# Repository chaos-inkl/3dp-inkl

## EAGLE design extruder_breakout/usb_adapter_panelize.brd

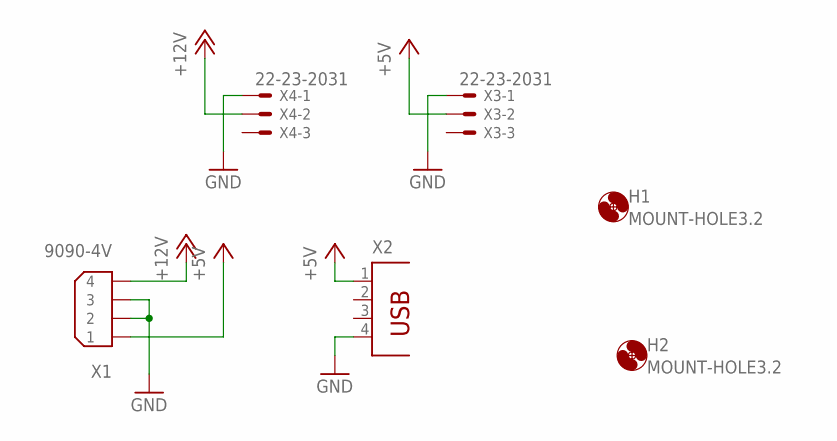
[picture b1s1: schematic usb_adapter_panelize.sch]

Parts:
H1, H2: MOUNT-HOLE3.2; 3,2
X1: 9090-4V
X2: PN87520
X3, X4: 22-23-2031

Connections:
+5V: X1.1, X2.1, X3.2
+12V: X1.4, X4.2
GND: X1.2, X1.3, X2.4, X3.1, X4.1

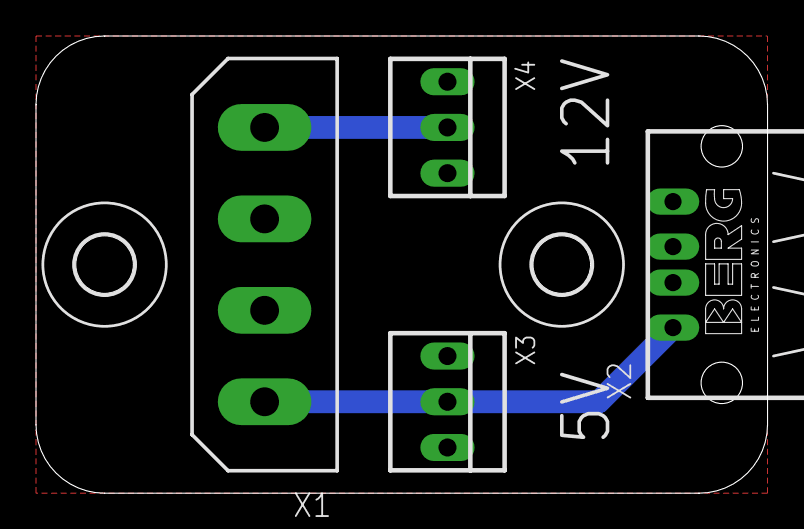
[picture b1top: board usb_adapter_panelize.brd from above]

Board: 2 copper layers, 40.6 x 25.4 mm, 6 parts (0 on the bottom side), 3 nets.

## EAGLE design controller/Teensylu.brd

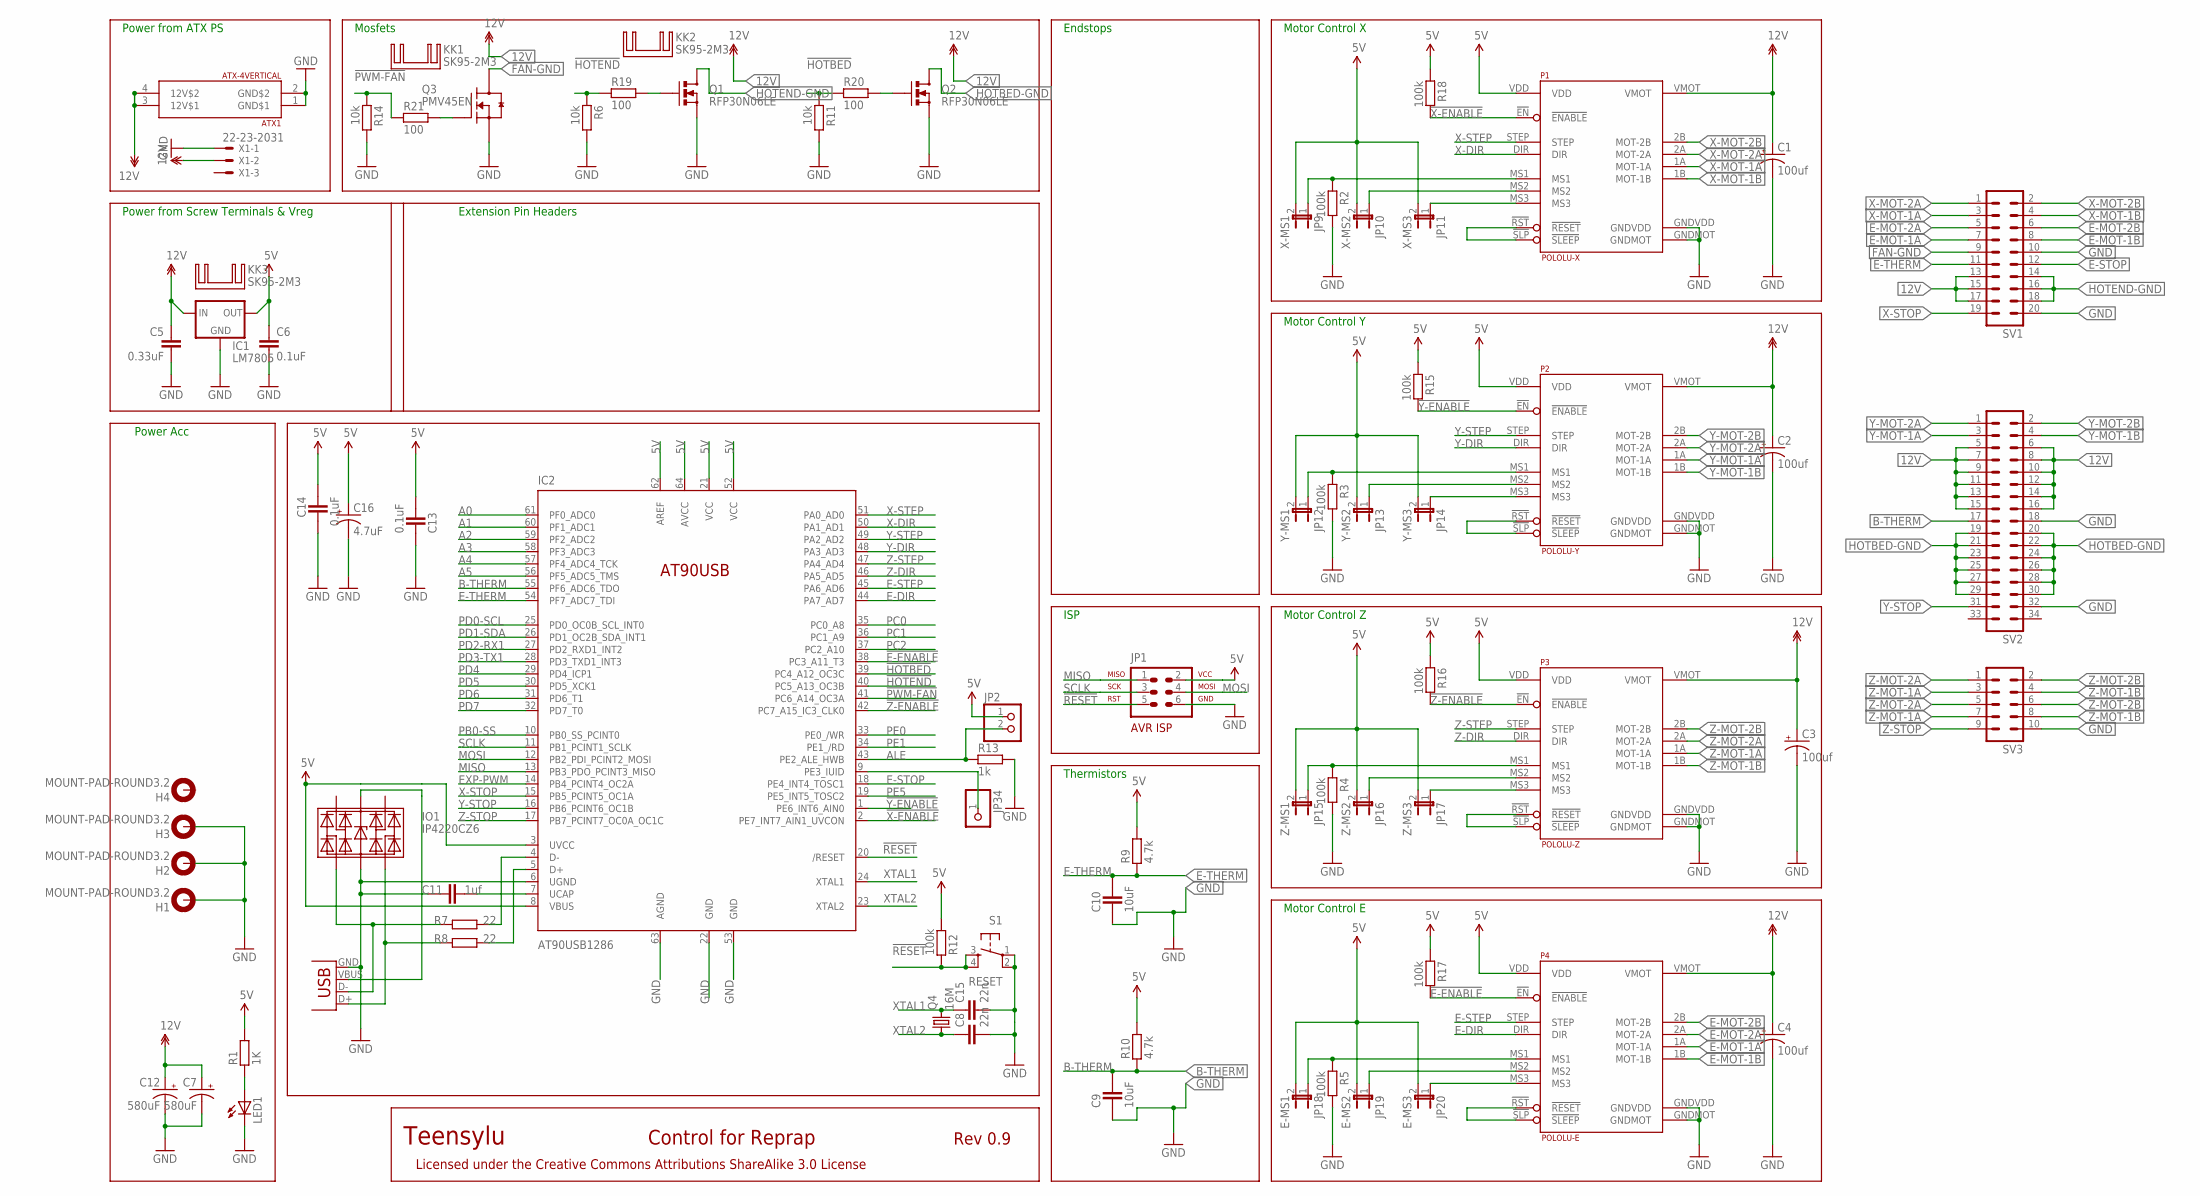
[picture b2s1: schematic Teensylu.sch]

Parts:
ATX1: ATX-4VERTICAL; MINIFITJR-4-VERTICAL
C1, C2, C3, C4: 100uf; CPOL-RADIAL-100UF-25V
C5: 0.33uF; CAP-PTH-SMALL2
C6: 0.1uF; CAP-PTH-SMALL2
C7, C12: 580uF; CPOL-RADIAL-1000UF-25V
C8, C15: 22n; C0603
C9, C10: 10uF; CAPC1608X92N
C11: 1uf; CAPC1608X92N
C13, C14: 0.1uF; CAPC1608X92N
C16: 4.7uF; CPOL-RADIAL-10UF-25V
H1, H2, H3, H4: MOUNT-PAD-ROUND3.2; 3,2-PAD
IC1: LM7805; 78XXL-CUSTOM
IC2: AT90USB1286; TQFP64-2
IO1: IP4220CZ6; SOT23-6
J1: USB; USB-B-PTH
JP1: AVR-ISP-6VERT; AVR-ISP-6
JP2: PINHD-1X2; 1X02
JP9: X-MS1; 1X02
JP10: X-MS2; 1X02
JP11: X-MS3; 1X02
JP12: Y-MS1; 1X02
JP13: Y-MS2; 1X02
JP14: Y-MS3; 1X02
JP15: Z-MS1; 1X02
JP16: Z-MS2; 1X02
JP17: Z-MS3; 1X02
JP18: E-MS1; 1X02
JP19: E-MS2; 1X02
JP20: E-MS3; 1X02
JP34: PINHD-1X1; 1X01
KK1, KK2, KK3: SK95-2M3
LED1: LED5MM
P1: POLOLU-X; POLOLU-ALLEGRO-PTH
P2: POLOLU-Y; POLOLU-ALLEGRO-PTH
P3: POLOLU-Z; POLOLU-ALLEGRO-PTH
P4: POLOLU-E; POLOLU-ALLEGRO-PTH
Q1, Q2: RFP30N06LE; TO220V
Q3: PMV45EN; SOT95P280X135-3N
Q4: 16M; HC49U-V
R1: 1K; RESC1608X55N
R2, R3, R4, R5, R12, R15, R16, R17, R18: 100k; RESC1608X55N
R6, R11, R14: 10k; RESC1608X55N
R7, R8: 22; RESC1608X55N
R9, R10: 4.7k; RESC1608X55N
R13: 1k; RESC1608X55N
R19, R20, R21: 100; RESC1608X55N
S1: RESET; TACTILE-PTH
SV1: ML20L
SV2: ML34L
SV3: ML10L
X1: 22-23-2031

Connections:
5V: C6.1, C13.2, C14.1, C16.1 (+), IC1.OUT, IC2.3 (UVCC), IC2.8 (VBUS), IC2.21 (VCC), IC2.52 (VCC), IC2.62 (AREF), IC2.64 (AVCC), JP1.2, JP2.1, JP9.2, JP10.2, JP11.2, JP12.2, JP13.2, JP14.2, JP15.2, JP16.2, JP17.2, JP18.2, JP19.2, JP20.2, P1.VDD, P2.VDD, P3.VDD, P4.VDD, R1.2, R9.2, R10.2, R12.2, R15.1, R16.1, R17.1, R18.1
12V: ATX1.3 (12V$1), ATX1.4 (12V$2), C1.1 (+), C2.1 (+), C3.1 (+), C4.1 (+), C5.1, C7.1 (+), C12.1 (+), IC1.IN, P1.VMOT, P2.VMOT, P3.VMOT, P4.VMOT, SV1.13, SV1.15, SV1.17, SV2.5, SV2.6, SV2.7, SV2.8, SV2.9, SV2.10, SV2.11, SV2.12, SV2.13, SV2.14, SV2.15, SV2.16, X1.2
!E-ENABLE: IC2.38 (PC3_A11_T3), P4.!EN (!ENABLE), R17.2
!HOTBED: IC2.39 (PC4_A12_OC3C), R11.1, R20.1
!HOTEND: IC2.40 (PC5_A13_OC3B), R6.1, R19.1
!PWM-FAN: IC2.41 (PC6_A14_OC3A), R14.1, R21.1
!RESET: IC2.20 (/RESET), JP1.5, R12.1, S1.3, S1.4
!X-ENABLE: IC2.2 (PE7_INT7_AIN1_UVCON), P1.!EN (!ENABLE), R18.2
!Y-ENABLE: IC2.1 (PE6_INT6_AIN0), P2.!EN (!ENABLE), R15.2
!Z-ENABLE: IC2.42 (PC7_A15_IC3_CLK0), P3.!EN (!ENABLE), R16.2
A0: IC2.61 (PF0_ADC0)
A1: IC2.60 (PF1_ADC1)
A2: IC2.59 (PF2_ADC2)
A3: IC2.58 (PF3_ADC3)
A4: IC2.57 (PF4_ADC4_TCK)
A5: IC2.56 (PF5_ADC5_TMS)
ALE: IC2.43 (PE2_ALE_HWB), JP2.2, R13.1
B-THERM: C9.2, IC2.55 (PF6_ADC6_TDO), R10.1, SV2.17
E-DIR: IC2.44 (PA7_AD7), P4.DIR
E-MOT-1A: P4.1A (MOT-1A), SV1.7
E-MOT-1B: P4.1B (MOT-1B), SV1.8
E-MOT-2A: P4.2A (MOT-2A), SV1.5
E-MOT-2B: P4.2B (MOT-2B), SV1.6
E-MS1: JP18.1, P4.MS1, R5.1
E-MS2: JP19.1, P4.MS2
E-MS3: JP20.1, P4.MS3
E-RESETSLEEP: P4.!RST (!RESET), P4.!SLP (!SLEEP)
E-STEP: IC2.45 (PA6_AD6), P4.STEP
E-STOP: IC2.18 (PE4_INT4_TOSC1), SV1.12
E-THERM: C10.2, IC2.54 (PF7_ADC7_TDI), R9.1, SV1.11
EXP-PWM: IC2.14 (PB4_PCINT4_OC2A)
FAN-GND: Q3.3 (D), SV1.9
GND: ATX1.1 (GND$1), ATX1.2 (GND$2), C1.2 (-), C2.2 (-), C3.2 (-), C4.2 (-), C5.2, C6.2, C7.2 (-), C8.2, C9.1, C10.1, C11.1, C12.2 (-), C13.1, C14.2, C15.2, C16.2 (-), H1.B3,2, H2.B3,2, H3.B3,2, IC1.GND, IC2.6 (UGND), IC2.22 (GND), IC2.53 (GND), IC2.63 (AGND), IO1.2 (GND), J1.GND, JP1.6, LED1.K (C), P1.GNDMOT, P1.GNDVDD, P2.GNDMOT, P2.GNDVDD, P3.GNDMOT, P3.GNDVDD, P4.GNDMOT, P4.GNDVDD, Q1.3 (S), Q2.3 (S), Q3.2 (S), R2.2, R3.2, R4.2, R5.2, R6.2, R11.2, R13.2, R14.2, S1.1, S1.2, SV1.10, SV1.20, SV2.18, SV2.32, SV3.10, X1.1
HOTBED-GND: Q2.2 (D), SV2.19, SV2.20, SV2.21, SV2.22, SV2.23, SV2.24, SV2.25, SV2.26, SV2.27, SV2.28, SV2.29, SV2.30
HOTEND-GND: Q1.2 (D), SV1.14, SV1.16, SV1.18
MISO: IC2.13 (PB3_PDO_PCINT3_MISO), JP1.1
MOSI: IC2.12 (PB2_PDI_PCINT2_MOSI), JP1.4
unnamed: LED1.A, R1.1
unnamed: IO1.4 (C), J1.D-, R7.1
unnamed: IC2.4 (D-), R7.2
unnamed: IC2.5 (D+), R8.2
unnamed: IO1.6 (D), J1.D+, R8.1
unnamed: IO1.5 (UCC), J1.VBUS
unnamed: IC2.9 (PE3_IUID), JP34.1
unnamed: C11.2, IC2.7 (UCAP)
unnamed: Q3.1 (G), R21.2
unnamed: Q1.1 (G), R19.2
unnamed: Q2.1 (G), R20.2
PB0-SS: IC2.10 (PB0_SS_PCINT0)
PC0: IC2.35 (PC0_A8)
PC1: IC2.36 (PC1_A9)
PC2: IC2.37 (PC2_A10)
PD0-SCL: IC2.25 (PD0_OC0B_SCL_INT0)
PD1-SDA: IC2.26 (PD1_OC2B_SDA_INT1)
PD2-RX1: IC2.27 (PD2_RXD1_INT2)
PD3-TX1: IC2.28 (PD3_TXD1_INT3)
PD4: IC2.29 (PD4_ICP1)
PD5: IC2.30 (PD5_XCK1)
PD6: IC2.31 (PD6_T1)
PD7: IC2.32 (PD7_T0)
PE0: IC2.33 (PE0_/WR)
PE1: IC2.34 (PE1_/RD)
PE5: IC2.19 (PE5_INT5_TOSC2)
SCLK: IC2.11 (PB1_PCINT1_SCLK), JP1.3
X-DIR: IC2.50 (PA1_AD1), P1.DIR
X-MOT-1A: P1.1A (MOT-1A), SV1.3
X-MOT-1B: P1.1B (MOT-1B), SV1.4
X-MOT-2A: P1.2A (MOT-2A), SV1.1
X-MOT-2B: P1.2B (MOT-2B), SV1.2
X-MS1: JP9.1, P1.MS1, R2.1
X-MS2: JP10.1, P1.MS2
X-MS3: JP11.1, P1.MS3
X-RESETSLEEP: P1.!RST (!RESET), P1.!SLP (!SLEEP)
X-STEP: IC2.51 (PA0_AD0), P1.STEP
X-STOP: IC2.15 (PB5_PCINT5_OC1A), SV1.19
XTAL1: C15.1, IC2.24 (XTAL1), Q4.2
XTAL2: C8.1, IC2.23 (XTAL2), Q4.1
Y-DIR: IC2.48 (PA3_AD3), P2.DIR
Y-MOT-1A: P2.1A (MOT-1A), SV2.3
Y-MOT-1B: P2.1B (MOT-1B), SV2.4
Y-MOT-2A: P2.2A (MOT-2A), SV2.1
Y-MOT-2B: P2.2B (MOT-2B), SV2.2
Y-MS1: JP12.1, P2.MS1, R3.1
Y-MS2: JP13.1, P2.MS2
Y-MS3: JP14.1, P2.MS3
Y-RESETSLEEP: P2.!RST (!RESET), P2.!SLP (!SLEEP)
Y-STEP: IC2.49 (PA2_AD2), P2.STEP
Y-STOP: IC2.16 (PB6_PCINT6_OC1B), SV2.31
Z-DIR: IC2.46 (PA5_AD5), P3.DIR
Z-MOT-1A: P3.1A (MOT-1A), SV3.3, SV3.7
Z-MOT-1B: P3.1B (MOT-1B), SV3.4, SV3.8
Z-MOT-2A: P3.2A (MOT-2A), SV3.1, SV3.5
Z-MOT-2B: P3.2B (MOT-2B), SV3.2, SV3.6
Z-MS1: JP15.1, P3.MS1, R4.1
Z-MS2: JP16.1, P3.MS2
Z-MS3: JP17.1, P3.MS3
Z-RESETSLEEP: P3.!RST (!RESET), P3.!SLP (!SLEEP)
Z-STEP: IC2.47 (PA4_AD4), P3.STEP
Z-STOP: IC2.17 (PB7_PCINT7_OC0A_OC1C), SV3.9

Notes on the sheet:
Motor Control X
Motor Control Y
Motor Control Z
Motor Control E
ISP
Thermistors
Endstops
Mosfets
Power Acc
Teensylu
Rev 0.9
Control for Reprap
Licensed under the Creative Commons Attributions ShareAlike 3.0 License
Extension Pin Headers
Power from ATX PS
Power from Screw Terminals & Vreg

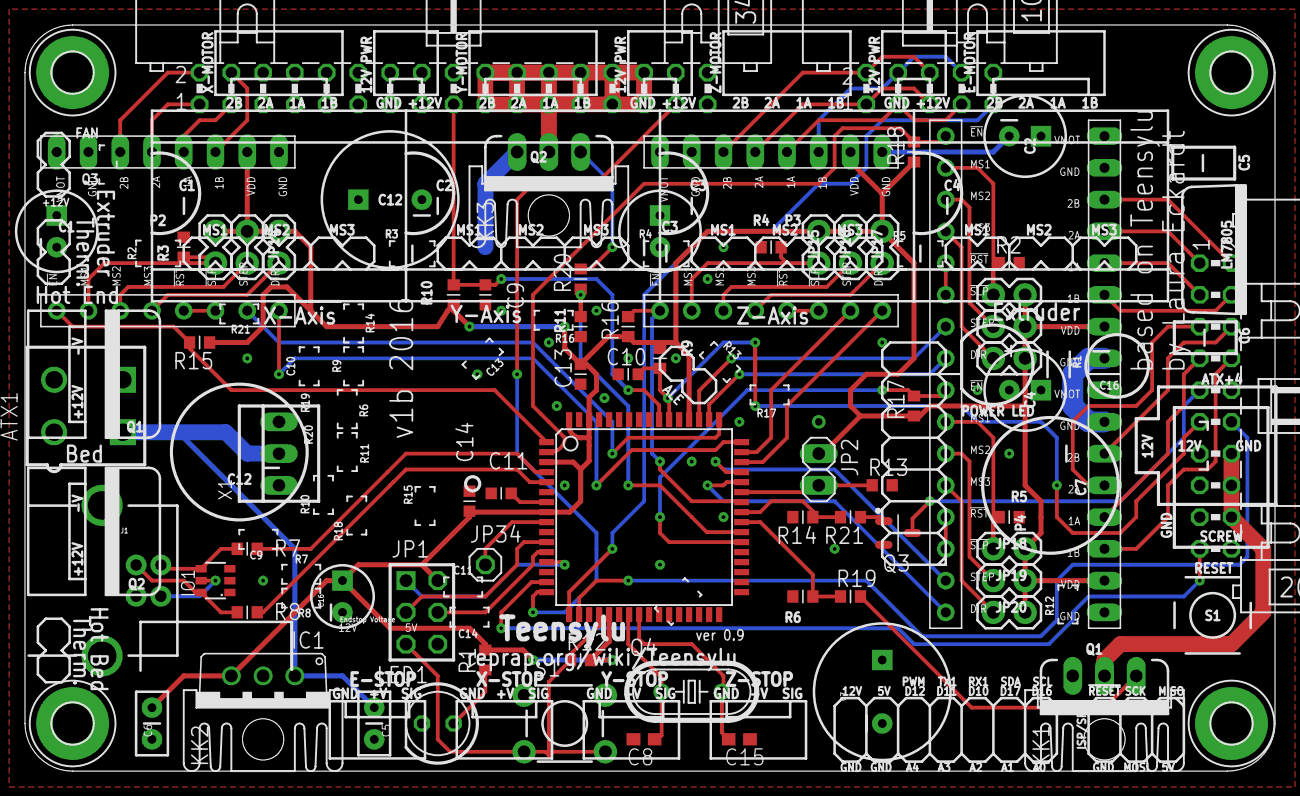
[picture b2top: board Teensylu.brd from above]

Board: 2 copper layers, 100.0 x 59.7 mm, 78 parts (0 on the bottom side), 77 nets.

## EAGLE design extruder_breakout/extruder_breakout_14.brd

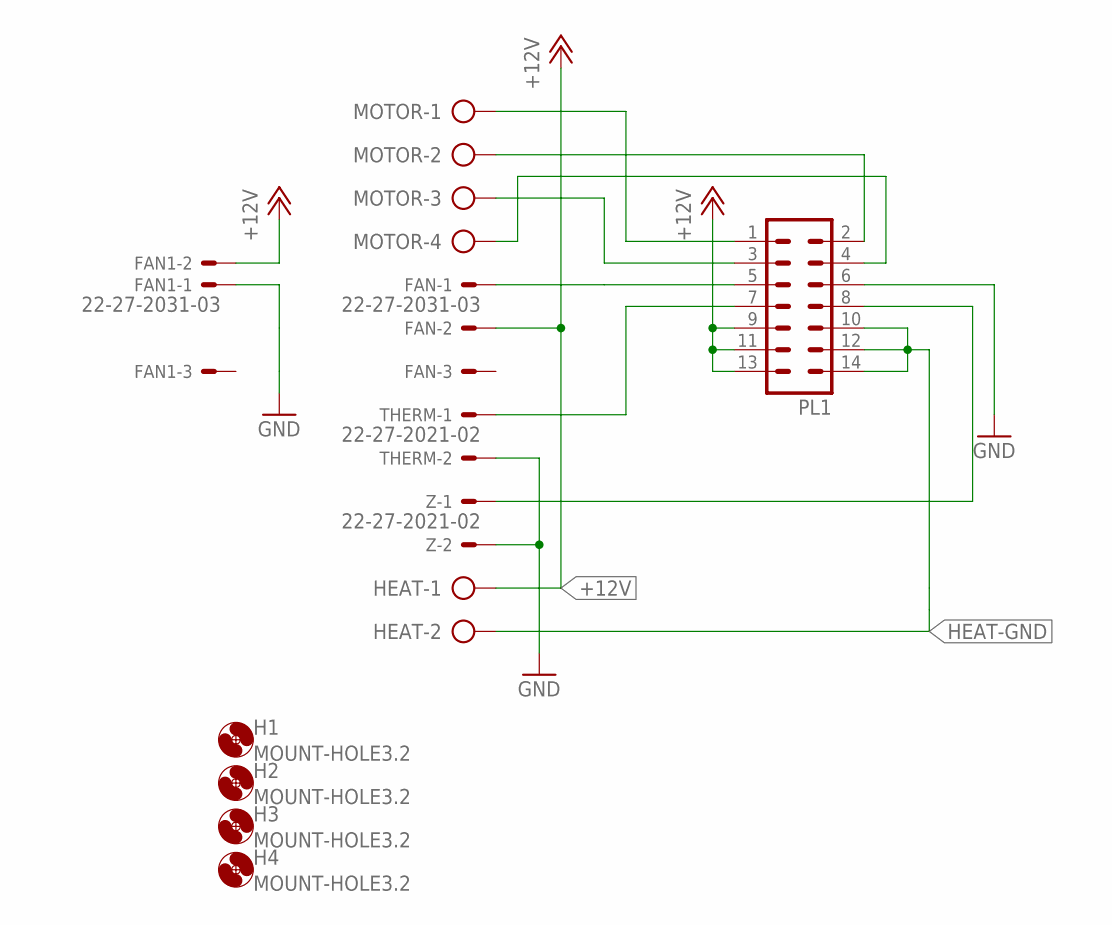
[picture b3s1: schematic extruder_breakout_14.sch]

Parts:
FAN, FAN1: 22-27-2031-03; 6410-03
H1, H2, H3, H4: MOUNT-HOLE3.2; 3,2
HEAT: AK500/2
MOTOR: AK500/4
PL1: 14V
THERM: 22-27-2021-02; 6410-02
Z: 22-27-2021-02; 6410-02

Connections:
+12V: FAN.2, FAN1.2, HEAT.1, PL1.9, PL1.11, PL1.13
GND: FAN1.1, PL1.6, THERM.2, Z.2
HEAT-GND: HEAT.2, PL1.10, PL1.12, PL1.14
unnamed: MOTOR.1, PL1.1
unnamed: MOTOR.2, PL1.2
unnamed: MOTOR.3, PL1.3
unnamed: MOTOR.4, PL1.4
unnamed: FAN.1, PL1.5
unnamed: PL1.7, THERM.1
unnamed: PL1.8, Z.1

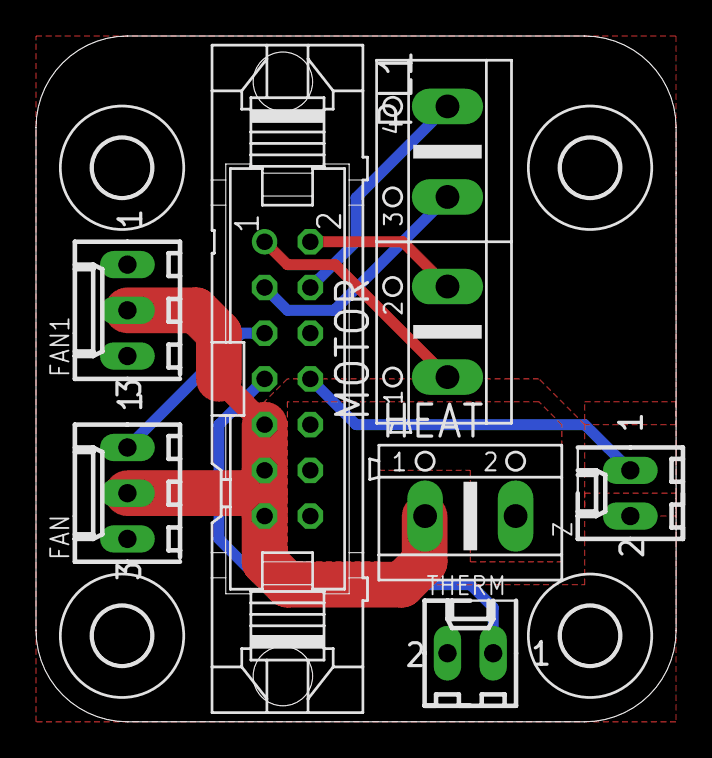
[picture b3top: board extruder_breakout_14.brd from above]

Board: 2 copper layers, 35.6 x 38.1 mm, 11 parts (0 on the bottom side), 10 nets.

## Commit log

2015-07-31 added all design files for our 3D printer
2015-07-31 moved files to subdirectory
2015-08-26 added missing z-axis coupler
2016-05-04 neue, vertikale x-Achse hinzugefügt
2016-05-04 extruder breakout boards hinzugefügt
2016-05-04 unsere variante des Teensylu controllers hinzugefügt
2016-05-04 sicherungsdateien von eagle nicht ins repo aufnehmen
2016-06-02 behebt kleine Fehler im Stromverteiler-Board
2016-06-03 add power-clip
2016-06-06 power-clip: resize holes
2016-06-13 Loch für M8-Mutter vergrößert
2016-06-30 Add M5 version of x-end-tensioner
2016-07-26 add x-carriage-pk
2016-08-07 extruder-body rotate and cable clip
2016-08-12 some more printer parts
2017-02-23 Add additional parts from thingiverse
2017-02-23 Fix formatting in README.md
2017-02-23 Add mounting bracket for reichelt LCD display
2017-02-23 Fix formatting in README.md (again)
2017-02-23 Add mounting plate for Raspberry Pi B+/2/3
2017-03-01 resolve dependency for nutsnbolts
2017-04-24 Update mounting plate for Raspberry Pi
    Improvements:
    - Longer standoffs to have all four USB ports available
    - Cutouts to mount M2.5 hex screws from bottom-up
    - Changed mounting to printer and cutout in the middle to save more filament
2017-05-03 Add spacers for Pi HAT
